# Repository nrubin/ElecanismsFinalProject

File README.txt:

Kinetic Tree Sculpture 
======
by Shivam Desai, Asa Eckert-Erdheim, Katherine Stegner, Noam Rubin

Kinetic sculpture of a living tree that visualizes user input through growth and decay

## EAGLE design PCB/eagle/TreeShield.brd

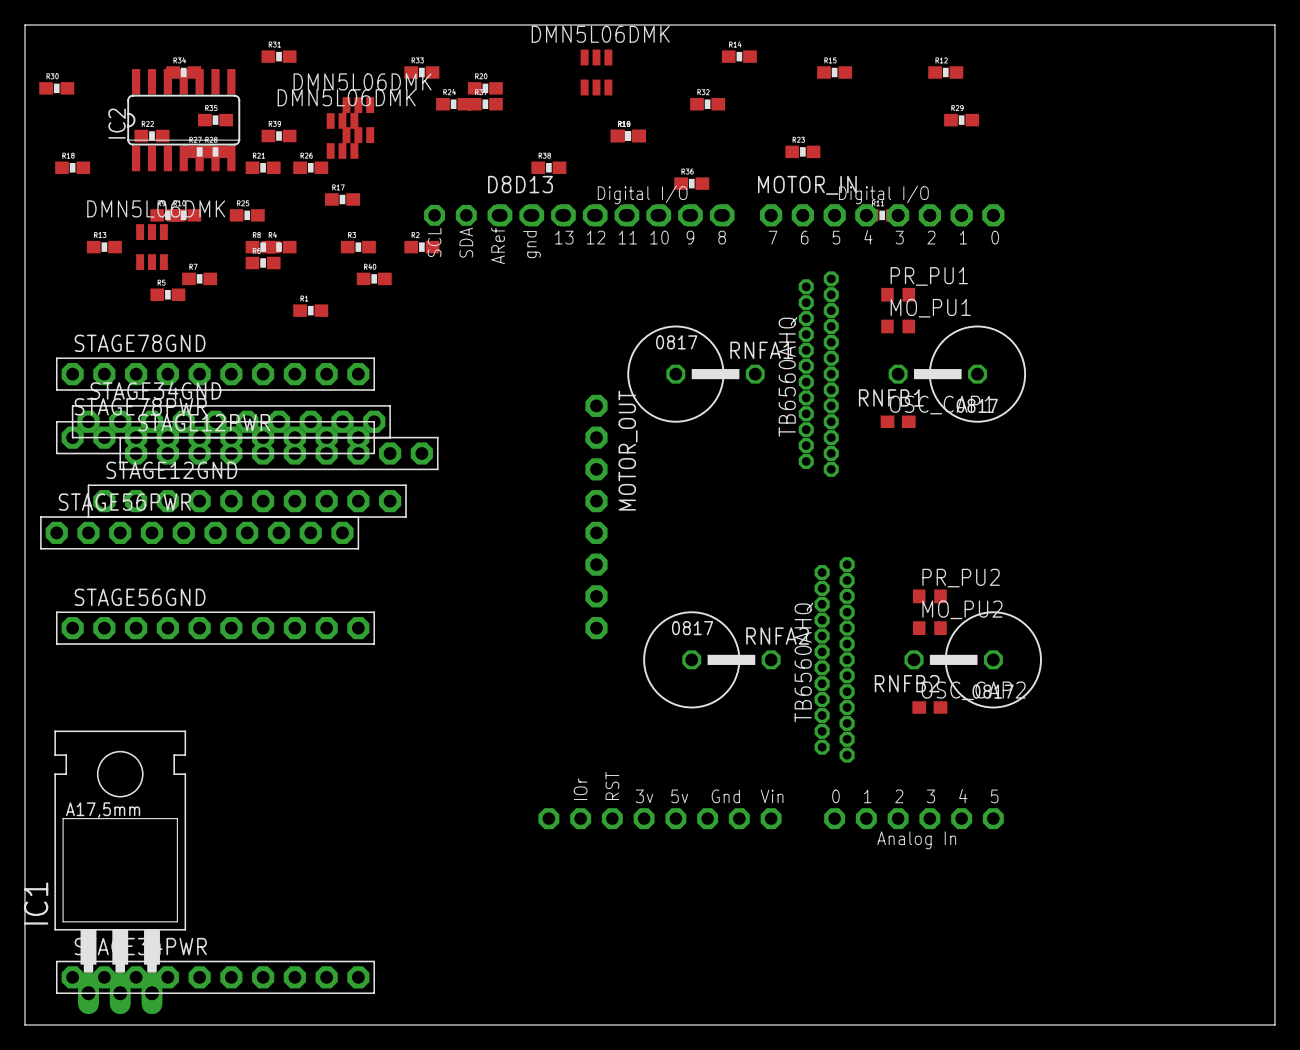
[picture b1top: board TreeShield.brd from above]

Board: 2 copper layers, 100.0 x 80.0 mm, 70 parts (0 on the bottom side), 90 nets, no tracks yet.

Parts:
D8D13: 1X08-CLEANBIG
IC1: LM1117T-5.0; TO220
IC2: 74HC164D; SO14
MOTOR1, MOTOR2: TB6560AHQ
MOTOR_IN: 1X08-CLEANBIG
MOTOR_OUT: 1X08-CLEANBIG
MO_PU1, MO_PU2: 1k; R0603
OSC_CAP1, OSC_CAP2: 100p; C0603
PR_PU1, PR_PU2: 1k; R0603
R1, R2, R3, R4, R5, R6, R7, R8, R9, R10, R11, R12, R13, R14, R15, R16, R17, R18, R19, R20, R21, R22, R23, R24, R25, R26, R27, R28, R29, R30, R31, R32, R33, R34, R35, R36, R37, R38, R39, R40: 0603-RES
RNFA1, RNFA2: 0.4; P0817V
RNFB1, RNFB2: 0.4; P0817V
STAGE12GND, STAGE12PWR, STAGE34GND, STAGE34PWR, STAGE56GND, STAGE56PWR, STAGE78GND, STAGE78PWR: PINHD-1X10; 1X10-BIG
U1: ARDUINOR3-BPLACE
U$1, U$2, U$3, U$4: DMN5L06DMK

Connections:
CLK1: MOTOR1.CLK, MOTOR_IN.4
CW1: MOTOR1.CW/CCW, MOTOR_IN.1
EN1: MOTOR1.ENABLE, MOTOR_IN.3
GND: IC1.1, IC2.7, MOTOR1.DCY1, MOTOR1.DCY2, MOTOR1.M1, MOTOR1.M2, MOTOR1.PGNDA, MOTOR1.PGNDB, MOTOR1.SGND, MOTOR1.TQ1, MOTOR1.TQ2, MOTOR2.DCY1, MOTOR2.DCY2, MOTOR2.M1, MOTOR2.M2, MOTOR2.PGNDA, MOTOR2.PGNDB, MOTOR2.SGND, MOTOR2.TQ1, MOTOR2.TQ2, OSC_CAP1.1, OSC_CAP2.1, RNFA1.2, RNFA2.2, RNFB1.2, RNFB2.2, STAGE34GND.1, STAGE34GND.2, STAGE34GND.3, STAGE34GND.4, STAGE34GND.5, STAGE34GND.6, STAGE34GND.7, STAGE34GND.8, STAGE34GND.9, STAGE34GND.10, STAGE56GND.1, STAGE56GND.2, STAGE56GND.3, STAGE56GND.4, STAGE56GND.5, STAGE56GND.6, STAGE56GND.7, STAGE56GND.8, STAGE56GND.9, STAGE56GND.10, STAGE78GND.1, STAGE78GND.2, STAGE78GND.3, STAGE78GND.4, STAGE78GND.5, STAGE78GND.6, STAGE78GND.7, STAGE78GND.8, STAGE78GND.9, STAGE78GND.10, U1.GND, U$1.D1, U$1.D2, U$2.D1, U$2.D2, U$3.D1, U$3.D2, U$4.D1, U$4.D2
unnamed: D8D13.1, IC2.1
unnamed: D8D13.2, IC2.2
unnamed: MOTOR1.NFA, RNFA1.1
unnamed: MOTOR1.MO, MO_PU1.1
unnamed: MOTOR1.PROTECT, PR_PU1.1
unnamed: MOTOR1.OSC, OSC_CAP1.2
unnamed: R1.2, STAGE12PWR.1
unnamed: R2.2, STAGE12PWR.2
unnamed: MOTOR1.NFB, RNFB1.1
unnamed: MOTOR2.CW/CCW, MOTOR_IN.5
unnamed: MOTOR2.RESET'', MOTOR_IN.6
unnamed: MOTOR2.ENABLE, MOTOR_IN.7
unnamed: MOTOR2.CLK, MOTOR_IN.8
unnamed: MOTOR2.NFB, RNFB2.1
unnamed: MOTOR2.NFA, RNFA2.1
unnamed: MOTOR2.MO, MO_PU2.1
unnamed: MOTOR2.OSC, OSC_CAP2.2
unnamed: MOTOR2.PROTECT, PR_PU2.1
unnamed: R3.2, STAGE12PWR.3
unnamed: R4.2, STAGE12PWR.4
unnamed: R5.2, STAGE12PWR.5
unnamed: R6.2, STAGE12PWR.6
unnamed: R7.2, STAGE12PWR.7
unnamed: R8.2, STAGE12PWR.8
unnamed: D8D13.3, IC2.8
unnamed: D8D13.4, IC2.9
unnamed: IC2.3, U$2.G1
unnamed: IC2.4, U$2.G2
unnamed: IC2.5, U$1.G1
unnamed: IC2.6, U$1.G2
unnamed: R9.2, STAGE12PWR.9
unnamed: R10.2, STAGE12PWR.10
unnamed: R1.1, R2.1, R3.1, R4.1, R5.1, U$2.S1
unnamed: R6.1, R7.1, R8.1, R9.1, R10.1, U$2.S2
unnamed: R11.2, STAGE34PWR.1
unnamed: R12.2, STAGE34PWR.2
unnamed: R13.2, STAGE34PWR.3
unnamed: R14.2, STAGE34PWR.4
unnamed: R15.2, STAGE34PWR.5
unnamed: R16.2, STAGE34PWR.6
unnamed: R17.2, STAGE34PWR.7
unnamed: R18.2, STAGE34PWR.8
unnamed: R19.2, STAGE34PWR.9
unnamed: R20.2, STAGE34PWR.10
unnamed: R21.2, STAGE56PWR.1
unnamed: R22.2, STAGE56PWR.2
unnamed: R23.2, STAGE56PWR.3
unnamed: R24.2, STAGE56PWR.4
unnamed: R25.2, STAGE56PWR.5
unnamed: R26.2, STAGE56PWR.6
unnamed: R27.2, STAGE56PWR.7
unnamed: R28.2, STAGE56PWR.8
unnamed: R29.2, STAGE56PWR.9
unnamed: R30.2, STAGE56PWR.10
unnamed: R31.2, STAGE78PWR.1
unnamed: R32.2, STAGE78PWR.2
unnamed: R33.2, STAGE78PWR.3
unnamed: R34.2, STAGE78PWR.4
unnamed: R35.2, STAGE78PWR.5
unnamed: R36.2, STAGE78PWR.6
unnamed: R37.2, STAGE78PWR.7
unnamed: R38.2, STAGE78PWR.8
unnamed: R39.2, STAGE78PWR.9
unnamed: R40.2, STAGE78PWR.10
unnamed: R11.1, R12.1, R13.1, R14.1, R15.1, U$1.S1
unnamed: IC2.13, U$3.G2
unnamed: IC2.12, U$3.G1
unnamed: IC2.11, U$4.G2
unnamed: IC2.10, U$4.G1
unnamed: R16.1, R17.1, R18.1, R19.1, R20.1, U$1.S2
unnamed: R21.1, R22.1, R23.1, R24.1, R25.1, U$4.S1
unnamed: R26.1, R27.1, R28.1, R29.1, R30.1, U$4.S2
unnamed: R31.1, R32.1, R33.1, R34.1, R35.1, U$3.S1
unnamed: R36.1, R37.1, R38.1, R39.1, R40.1, U$3.S2
unnamed: STAGE12GND.1, STAGE12GND.2, STAGE12GND.3, STAGE12GND.4, STAGE12GND.5, STAGE12GND.6, STAGE12GND.7, STAGE12GND.8, STAGE12GND.9, STAGE12GND.10
OUT_AM1: MOTOR1.OUT_AM, MOTOR_OUT.3
OUT_AM2: MOTOR2.OUT_AM, MOTOR_OUT.7
OUT_AP1: MOTOR1.OUT_AP, MOTOR_OUT.4
OUT_AP2: MOTOR2.OUT_AP, MOTOR_OUT.8
OUT_BM1: MOTOR1.OUT_BM, MOTOR_OUT.1
OUT_BM2: MOTOR2.OUT_BM, MOTOR_OUT.5
OUT_BP1: MOTOR1.OUT_BP, MOTOR_OUT.2
OUT_BP2: MOTOR2.OUT_BP, MOTOR_OUT.6
RESET1: MOTOR1.RESET'', MOTOR_IN.2
VCC: IC1.2, IC2.14, MOTOR1.VDD, MOTOR2.VDD, MO_PU1.2, MO_PU2.2, PR_PU1.2, PR_PU2.2
VDD: IC1.3, MOTOR1.VMA, MOTOR1.VMB, MOTOR2.VMA, MOTOR2.VMB

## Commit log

2013-11-11 Noam cant spell
2013-11-11 added ardcom, PIC libs, scons stuff, old SPI code, and some arduino code
2013-11-11 creted folder for reference docs
2013-11-11 changed ardcom source from miniproj3 to miniproj4
2013-11-11 val1 and val2 values are changing but are not correct yet
2013-11-12 test write permissions of repo
2013-11-12 Remove testing file
2013-11-17 Added spec sheet for voltage regulator package
2013-11-17 Datasheet for stepper motor
2013-11-18 No need for voltage regulator as we are using the Elecanisms board
2013-11-18 VigorMotorDriverDatasheet.pdf
    added driver datasheet
2013-11-18 added encoder datasheet
2013-11-21 eagle jazz added
2013-11-21 Added motor driver library
2013-11-21 added ALD1106 footprint to elecanisms.lbr
2013-11-21 fixed ref files
2013-11-21 added adafruit library with arduino parts
2013-11-21 added missing pins to stepper motor driver
2013-11-21 nMOS library
2013-11-21 just need to add 5V regulator to schematic
2013-12-01 schematic sort of done
2013-12-01 moved things
2013-12-01 created ToDo for PCB
2013-12-01 started schematic in express
2013-12-02 added voltage regulator datasheet
2013-12-02 updated express schematic with motor driver, regulator, dio, analogs
2013-12-02 motor driver schematic
2013-12-02 final board schematic
2013-12-02 PCB updates, fuck comments
2013-12-04 schematic with correct pin labels; pcb with correct components placed
2013-12-04 beginning traces
2013-12-04 labels to pins
2013-12-05 added spice files
2013-12-05 added RTL MOSes and resistors
2013-12-05 added Octal Buffer to ref_files
2013-12-05 usage of Octal Buffer instead of RTL Inverter, usage of ports
2013-12-06 fuck yeah we have a PCB
2013-12-06 skeleton for website
2013-12-06 fuck yeah we have a PCB again
2013-12-06 removed all right angles on small traces, added thick traces for high current ports (VMA/B, PGNDA/B, motor ports) and added awesome signature
2013-12-06 minor trace adjustments for straightness
2013-12-06 mods
2013-12-09 added gitignore and potentiometer datasheet
2013-12-09 added PIC pin labels doc
2013-12-09 beginning PIC code
2013-12-09 added stepper driver files, new gitignore
2013-12-09 beginning integration between stepperdriver.c and tree.c
2013-12-09 IT WORKS IT WORKS
2013-12-10 updates to tree.c still need to merge
2013-12-11 added images dir
2013-12-15 pot control works, limit switch detection hacked but working
2013-12-16 accumulator test script for averaging the potval
2013-12-16 motors are responding well to pot control
2013-12-16 jitter bug beat once again
2013-12-17 last commit
2013-12-17 test function for accumulator
2013-12-17 added static website files
2013-12-17 added some basic bootstrap code
2013-12-17 deleted shit
2013-12-17 the navbar now scrolls correctly
2013-12-18 navbar is nice, need to add scrollto and lazy image loading
2013-12-18 added lazy image loading, team section, and lorem ipsum text
2013-12-19 fixed hero unit, started adding intro content, googled otters
2013-12-20 added all text content, just need to add images and enforce lazy image DLing
2013-12-20 put index in root for gh-pages
2013-12-20 re-added carousel due to git issues
2013-12-20 fixed kat bio and footer
2013-12-20 fixed some typos
2018-10-02 images now hosted locally

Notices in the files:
parts and their libraries:
SparkFun-Resistors: Licensing: CC v3.0 Share-Alike You are welcome to use this library for commercial purposes.
